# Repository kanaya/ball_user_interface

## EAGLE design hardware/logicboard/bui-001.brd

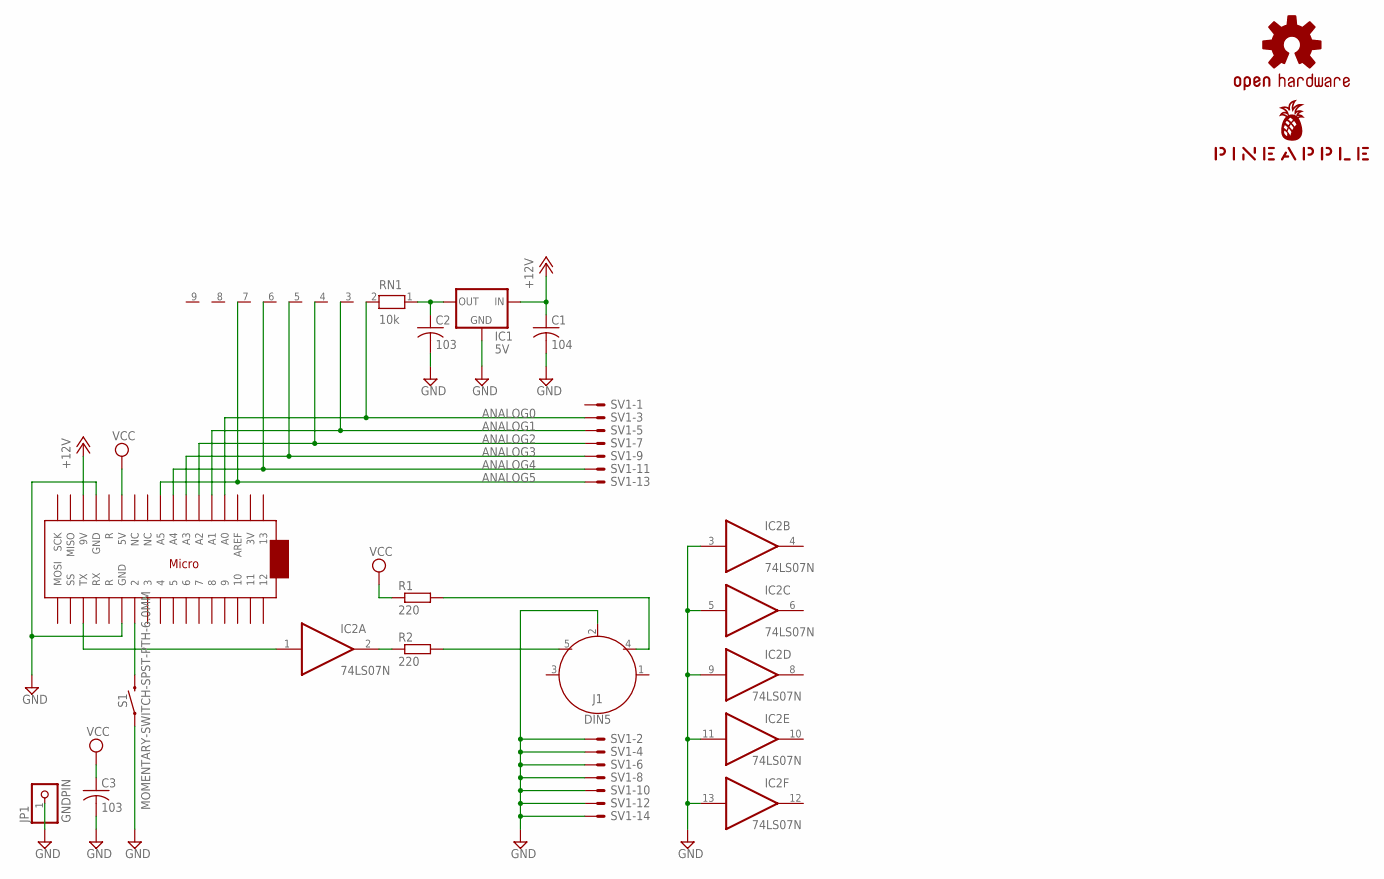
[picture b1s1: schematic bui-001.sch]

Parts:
C1: 104; C025-025X050
C2, C3: 103; C025-025X050
IC1: 5V; 78XXL
IC2: 74LS07N; DIL14
J1: DIN5; DIN5-RA-PTH
JP1: GNDPIN; 1X01
LOGO1: OSHW-LOGOS-COPPER; OSHW-LOGO-S_COPPER
MC1: ARDUINOMICRO
R1, R2: 220; 0204/5
RN1: 10k; RN-9
S1: MOMENTARY-SWITCH-SPST-PTH-6.0MM; TACTILE_SWITCH_PTH_6.0MM
SV1: ML14LE; ML14L
U$1: PINEAPPLE450_SILK

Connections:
+12V: C1.1, IC1.IN, MC1.P$20 (9V)
ANALOG0: MC1.P$31 (A0), RN1.2, SV1.3
ANALOG1: MC1.P$30 (A1), RN1.3, SV1.5
ANALOG2: MC1.P$29 (A2), RN1.4, SV1.7
ANALOG3: MC1.P$28 (A3), RN1.5, SV1.9
ANALOG4: MC1.P$27 (A4), RN1.6, SV1.11
ANALOG5: MC1.P$26 (A5), RN1.7, SV1.13
GND: C1.2, C2.2, C3.2, IC1.GND, IC2.3 (I), IC2.5 (I), IC2.7 (GND), IC2.9 (I), IC2.11 (I), IC2.13 (I), J1.2, JP1.1, MC1.P$12 (GND), MC1.P$21 (GND), S1.1, SV1.2, SV1.4, SV1.6, SV1.8, SV1.10, SV1.12, SV1.14
unnamed: MC1.P$11 (2), S1.3 (2)
unnamed: IC2.1 (I), MC1.P$15 (TX)
unnamed: IC2.2 (O), R2.1
unnamed: J1.5, R2.2
unnamed: J1.4, R1.2
VCC: C3.1, IC2.14 (VCC), MC1.P$23 (5V), R1.1
VOUT: C2.1, IC1.OUT, RN1.1

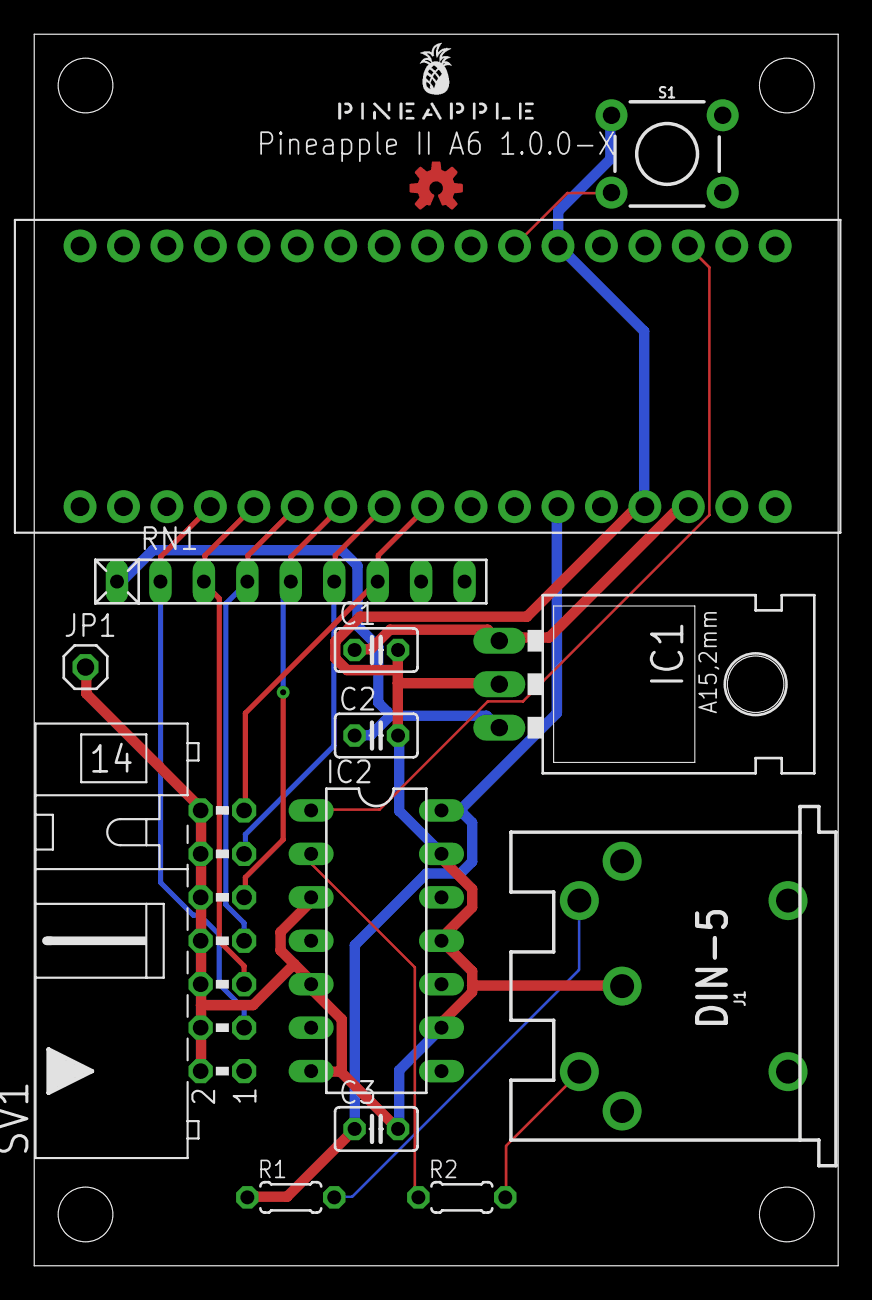
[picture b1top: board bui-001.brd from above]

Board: 2 copper layers, 47.0 x 72.0 mm, 15 parts (0 on the bottom side), 15 nets.

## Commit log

2020-01-09 Imported logicboard design from Pineapple II 2.0.2.
2020-01-09 Added .gitignore.
2020-01-09 Initial version of schematic.
2020-01-10 Finished schematic.
2020-01-11 INT switch.
2020-01-20 Moved all circuits to the center of the sheet for better looking.
2020-04-04 Screenshot.

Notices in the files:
parts and their libraries:
SparkFun-Connectors: Licensing: Creative Commons ShareAlike 4.0 International - https://creativecommons.org/licenses/by-sa/4.0
